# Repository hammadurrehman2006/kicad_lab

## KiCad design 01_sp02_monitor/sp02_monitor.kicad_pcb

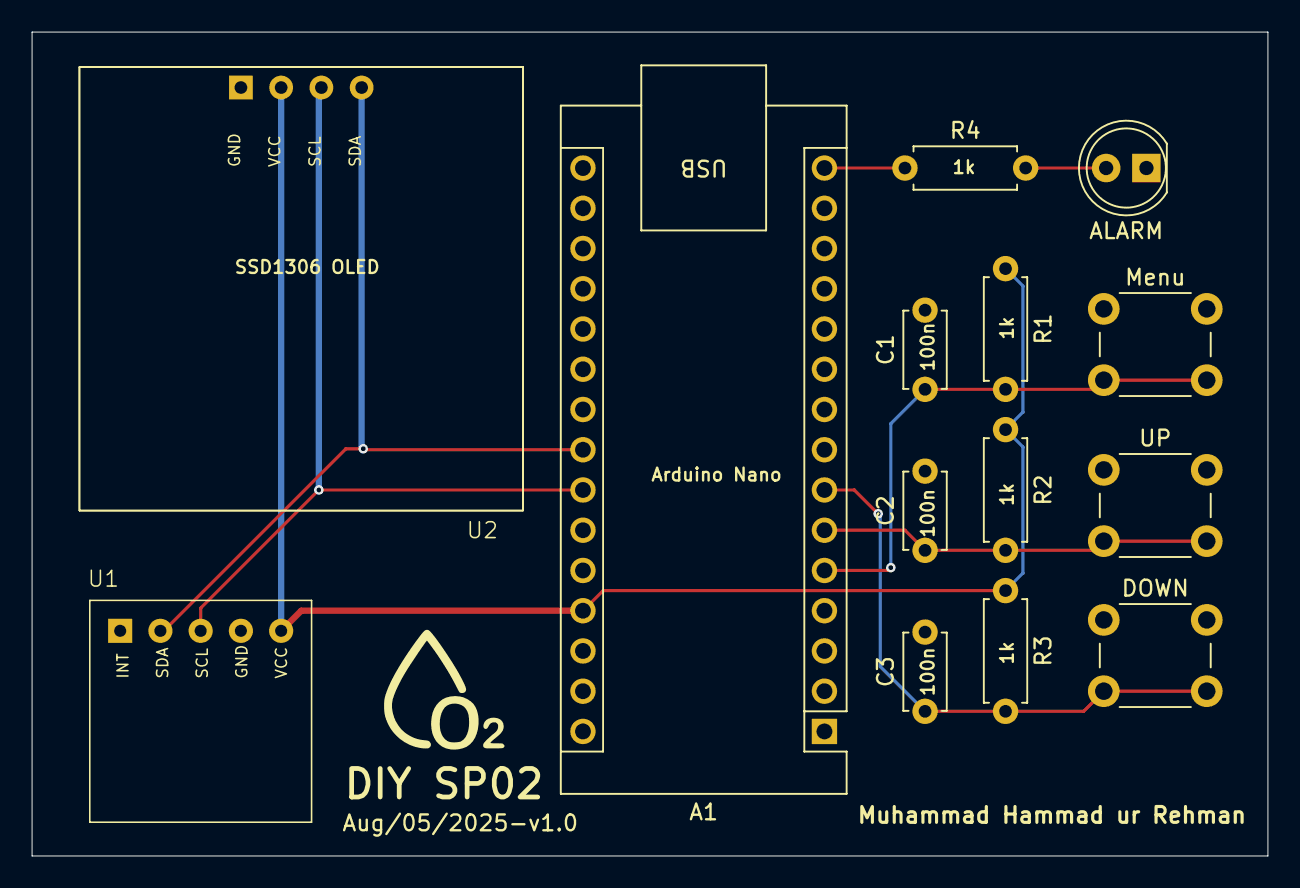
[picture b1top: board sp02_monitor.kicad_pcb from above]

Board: 4 copper layers, 78.0 x 52.0 mm, 14 parts (0 on the bottom side), 9 nets.

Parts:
A1: Arduino_Nano_v3.x; Arduino_Nano
ALARM: LED; LED_D5.0mm
C1, C2, C3: 100n; C_Disc_D4.7mm_W2.5mm_P5.00mm
DOWN: SW_Push; SW_PUSH_6mm
Menu: SW_Push; SW_PUSH_6mm
R1, R2, R3, R4: 1k; R_Axial_DIN0207_L6.3mm_D2.5mm_P7.62mm_Horizontal
U1: MAX30102; MAX30102_MODULE
U2: SSD1306
UP: SW_Push; SW_PUSH_6mm

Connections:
+5V: A1.27 (+5V), R1.1, R2.1, R3.1, U1.5 (VCC), U2.2 (VCC)
GND: A1.4 (GND), A1.29 (GND), ALARM.1 (K), C1.2, C2.2, C3.2, DOWN.1, Menu.1, U1.4 (GND), U2.1 (GND), UP.1
unnamed: A1.23 (A4), U1.2 (SDA), U2.4 (SDA)
unnamed: A1.24 (A5), U1.3 (SCL), U2.3 (SCL)
unnamed: A1.5 (D2), C1.1, Menu.2, R1.2
unnamed: A1.6 (D3), C2.1, R2.2, UP.2
unnamed: A1.7 (D4), C3.1, DOWN.2, R3.2
unnamed: A1.15 (D12), R4.1
unnamed: ALARM.2 (A), R4.2

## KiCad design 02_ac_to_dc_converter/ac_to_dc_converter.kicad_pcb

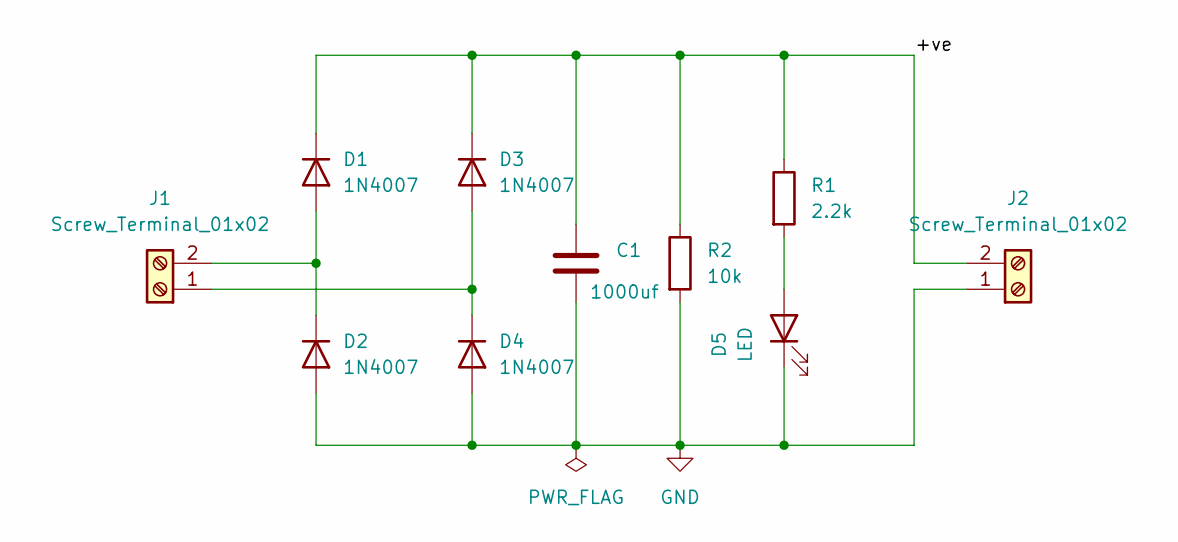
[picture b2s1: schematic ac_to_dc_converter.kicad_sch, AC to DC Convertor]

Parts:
C1: 1000uf; C_Radial_D8.0mm_H11.5mm_P3.50mm
D1, D2, D3, D4: 1N4007; D_DO-41_SOD81_P10.16mm_Horizontal
D5: LED; LED_D5.0mm
J1, J2: Screw_Terminal_01x02; TerminalBlock_bornier-2_P5.08mm
R1: 2.2k; R_Axial_DIN0207_L6.3mm_D2.5mm_P7.62mm_Horizontal
R2: 10k; R_Axial_DIN0207_L6.3mm_D2.5mm_P7.62mm_Horizontal

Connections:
/+ve: C1.1, D1.1 (K), D3.1 (K), J2.2, R1.1, R2.1
GND: C1.2, D2.2 (A), D4.2 (A), D5.1 (K), J2.1, R2.2
unnamed: D1.2 (A), D2.1 (K), J1.2
unnamed: D3.2 (A), D4.1 (K), J1.1
unnamed: D5.2 (A), R1.2

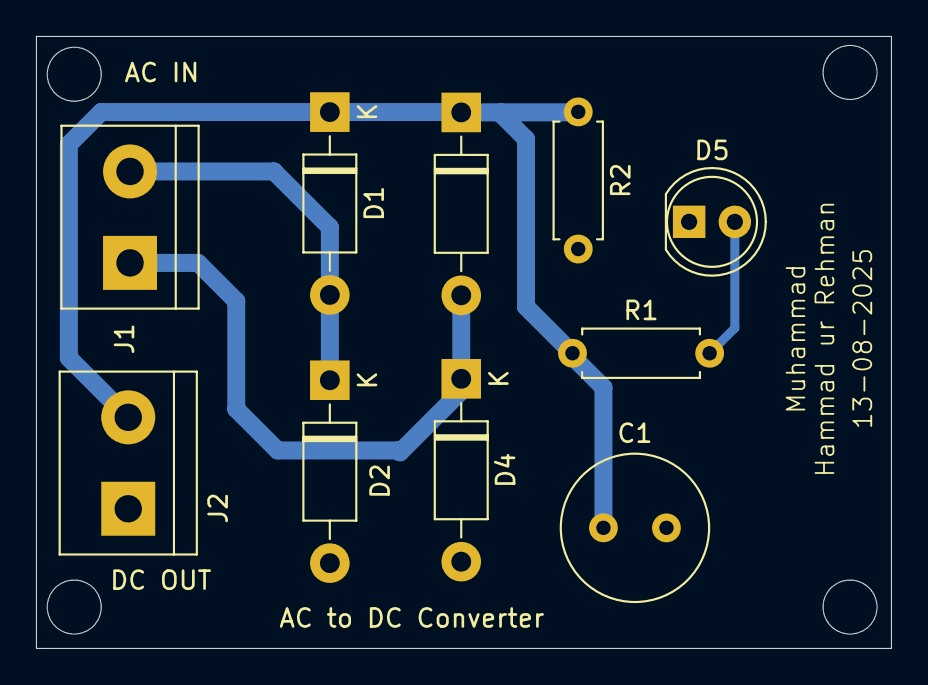
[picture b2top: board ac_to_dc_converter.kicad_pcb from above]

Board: 2 copper layers, 47.5 x 34.0 mm, 10 parts (0 on the bottom side), 5 nets.

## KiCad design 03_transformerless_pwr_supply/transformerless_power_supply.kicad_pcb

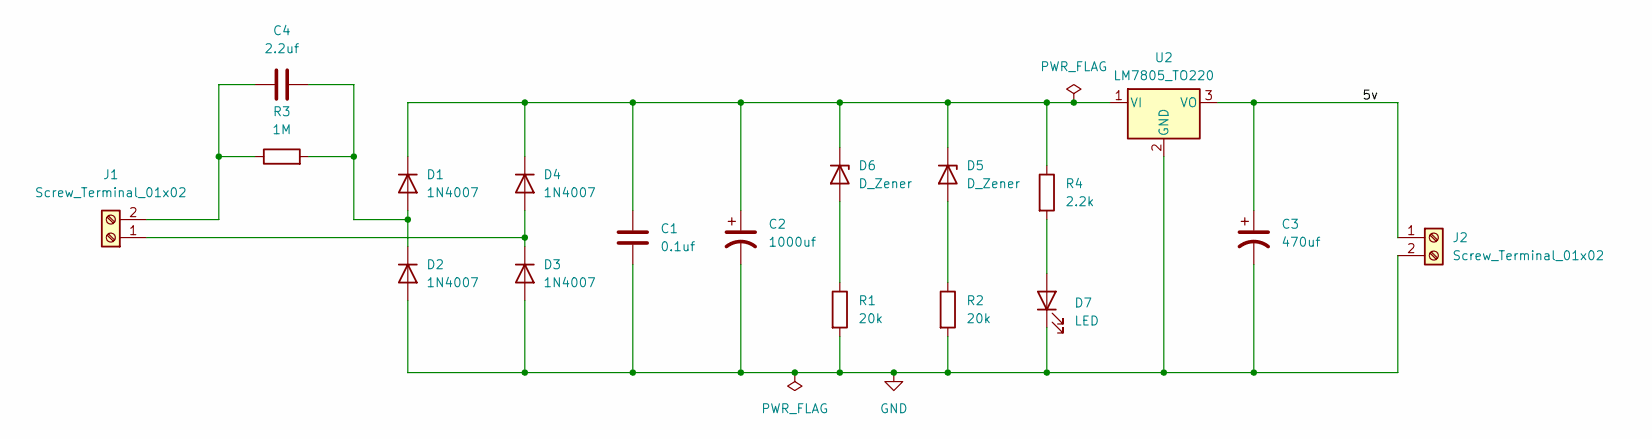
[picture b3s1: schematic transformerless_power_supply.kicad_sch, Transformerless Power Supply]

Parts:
C1: 0.1uf; C_Disc_D4.7mm_W2.5mm_P5.00mm
C2: 1000uf; CP_Radial_D10.0mm_P5.00mm
C3: 470uf; CP_Radial_D10.0mm_P3.80mm
C4: 2.2uf; C_Rect_L18.0mm_W6.0mm_P15.00mm_FKS3_FKP3
D1, D2, D3, D4: 1N4007; D_DO-41_SOD81_P10.16mm_Horizontal
D5, D6: D_Zener; D_A-405_P7.62mm_Horizontal
D7: LED; LED_D5.0mm
J1, J2: Screw_Terminal_01x02; TerminalBlock_bornier-2_P5.08mm
R1, R2: 20k; R_Axial_DIN0207_L6.3mm_D2.5mm_P7.62mm_Horizontal
R3: 1M; R_Axial_DIN0207_L6.3mm_D2.5mm_P7.62mm_Horizontal
R4: 2.2k; R_Axial_DIN0207_L6.3mm_D2.5mm_P7.62mm_Horizontal
U2: LM7805_TO220; TO-220-3_Vertical

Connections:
/5v: C3.1, J2.1, U2.3 (VO)
GND: C1.2, C2.2, C3.2, D2.2 (A), D3.2 (A), D7.1 (K), J2.2, R1.2, R2.2, U2.2 (GND)
unnamed: C4.2, D1.2 (A), D2.1 (K), R3.2
unnamed: C1.1, C2.1, D1.1 (K), D4.1 (K), D5.1 (K), D6.1 (K), R4.1, U2.1 (VI)
unnamed: D3.1 (K), D4.2 (A), J1.1
unnamed: D5.2 (A), R2.1
unnamed: D6.2 (A), R1.1
unnamed: D7.2 (A), R4.2
unnamed: C4.1, J1.2, R3.1

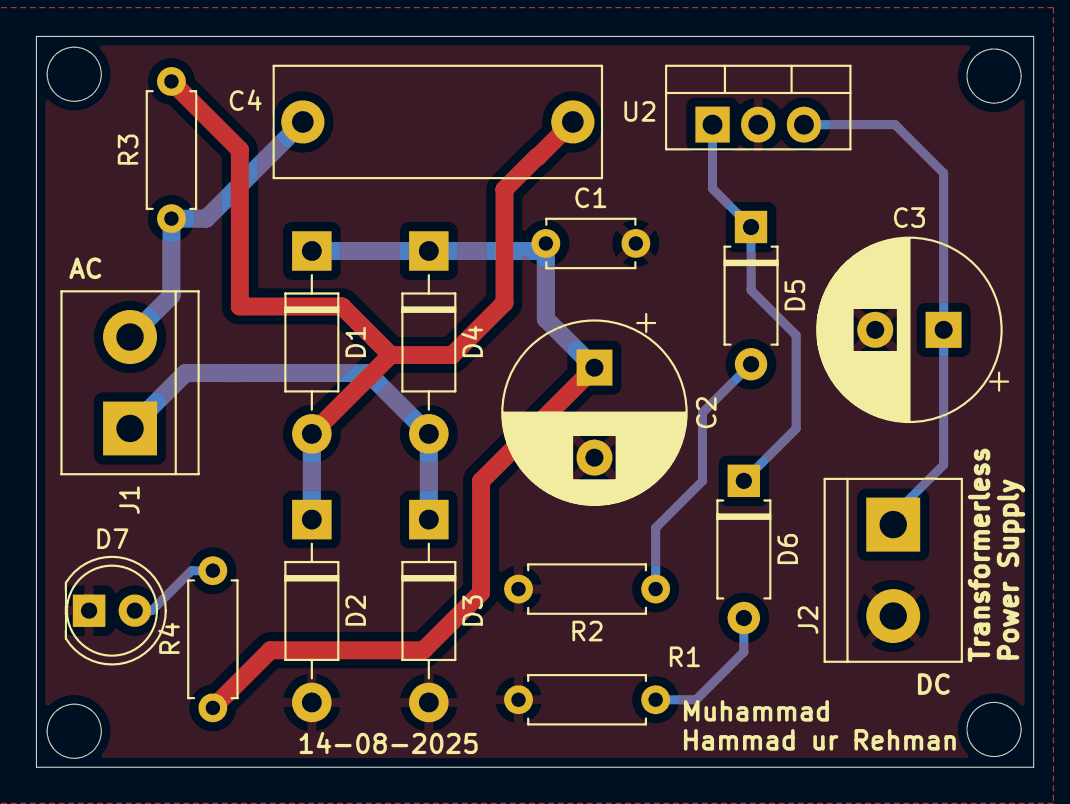
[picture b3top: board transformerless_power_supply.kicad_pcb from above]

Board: 2 copper layers, 55.4 x 40.6 mm, 18 parts (0 on the bottom side), 9 nets.
